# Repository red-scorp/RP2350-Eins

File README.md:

```
  _____  _____ ___  ____  _____  ___         ______ _____ _   _  _____ 
 |  __ \|  __ \__ \|___ \| ____|/ _ \       |  ____|_   _| \ | |/ ____|
 | |__) | |__) | ) | __) | |__ | | | |______| |__    | | |  \| | (___  
 |  _  /|  ___/ / / |__ <|___ \| | | |______|  __|   | | | . ` |\___ \ 
 | | \ \| |    / /_ ___) |___) | |_| |      | |____ _| |_| |\  |____) |
 |_|  \_\_|   |____|____/|____/ \___/       |______|_____|_| \_|_____/ 
```

# RP2350-Eins Project

The **RP2350-Eins** project aims to create a replacement for the Arduino UNO R3 or Arduino M0 using the RP2350 MCU.
This project was born as a continuation my previous project, [RP2040-Eins](https://github.com/red-scorp/RP2040-Eins), which was based on the Raspberry Pi RP2040 MCU.

## RP2350-Eins Board

The **RP2350-Eins** board is a 4-layer design intended to accommodate the popular Raspberry Pi RP2350 MCU within the standard Arduino UNO R3 footprint.

This board is crafted in Germany, and its name, "RP2350-Eins", incorporates the German word "Eins" (pronounced as "eye-ns"), which translates to "one". This name choice reflects the use of the same form-factor as the Arduino "Uno", which means "one" in Italian.

Preview:

You can view the [Schematics in PDF format](doc/RP2350-Eins.pdf) for detailed information.

STEP 3D file is available [with pins](doc/RP2350-Eins.step).

Features:

- Arduino UNO compatible pinout
- Partially compatible with Arduino Nano RP2350 Connect pinout
- Dual-core Cortex-M0+ Raspberry Pi RP2350
- 21 GPIO pins, including 4 analog inputs
- USB Type-C connector
- JTAG and DBG debugging connectors
- LDO-based 5V and 3.3V power supply with a maximum 12V input
- Supports both SOIC and WSON 16MB flash packages
- Includes power, user and RGB LEDs

CAM files, as well as the BOM and CPL files for JLCPCB, are available.

### Board Pinout

Following pinout is used for the board:

| Board Pin | RP2350 Pin | Function | Notes |
| --------- | ---------- | -------- | ----- |
| D0        | GPIO1      | UART0 TX |       |
| D1        | GPIO0      | UART0 RX |       |
| D2        | GPIO25     |          |       |
| D3        | GPIO15     |          |       |
| D4        | GPIO16     |          |       |
| D5        | GPIO17     |          |       |
| D6        | GPIO18     |          |       |
| D7        | GPIO19     |          |       |
| D8        | GPIO20     |          |       |
| D9        | GPIO21     |          |       |
| D10       | GPIO5      | SS       |       |
| D11       | GPIO7      | MOSI     |       |
| D12       | GPIO4      | MISO     |       |
| D13       | GPIO6      | SCK      | LED   |
| D14 A0    | GPIO26     |          |       |
| D15 A1    | GPIO27     |          |       |
| D16 A2    | GPIO28     |          |       |
| D17 A3    | GPIO29     |          |       |
| D18       | GPIO12     | SDA      |       |
| D19       | GPIO13     | SCL      |       |
| D20       | GPIO22     |          |       |
| D21       | GPIO23     |          |       |
| LED_R     | GPIO9      |          |       |
| LED_G     | GPIO10     |          |       |
| LED_B     | GPIO11     |          |       |

## Version History

This board exists in a single LDO-based flavor. If you want to use a Buck-based version of this board, please contact me directly.

Each version of the board listed below is tagged in the repository. You can use the tag to checkout the repository to the specific version.

### v1.0b1 - xx.xx.2024

Initial release for testing purposes.

## Links

- [Raspberry Pi RP2350 information page](https://www.raspberrypi.com/documentation/microcontrollers/silicon.html#rp2350).
- [Arduino UNO R3 information page](https://docs.arduino.cc/retired/boards/arduino-uno-rev3-with-long-pins).
- [Arduino SDK for RP2040/RP2350 board](https://github.com/earlephilhower/arduino-pico).

## How to Help

Your contributions as code, resources, or finances are welcome! Please contact me directly via email at andriy.golovnya@gmail.com or through my [GitHub profile](https://github.com/red-scorp).

If you'd like to make a financial contribution, you can donate via [PayPal](http://paypal.me/redscorp) or [Ko-Fi](http://ko-fi.com/redscorp). Your support is greatly appreciated.

Thanks in advance!

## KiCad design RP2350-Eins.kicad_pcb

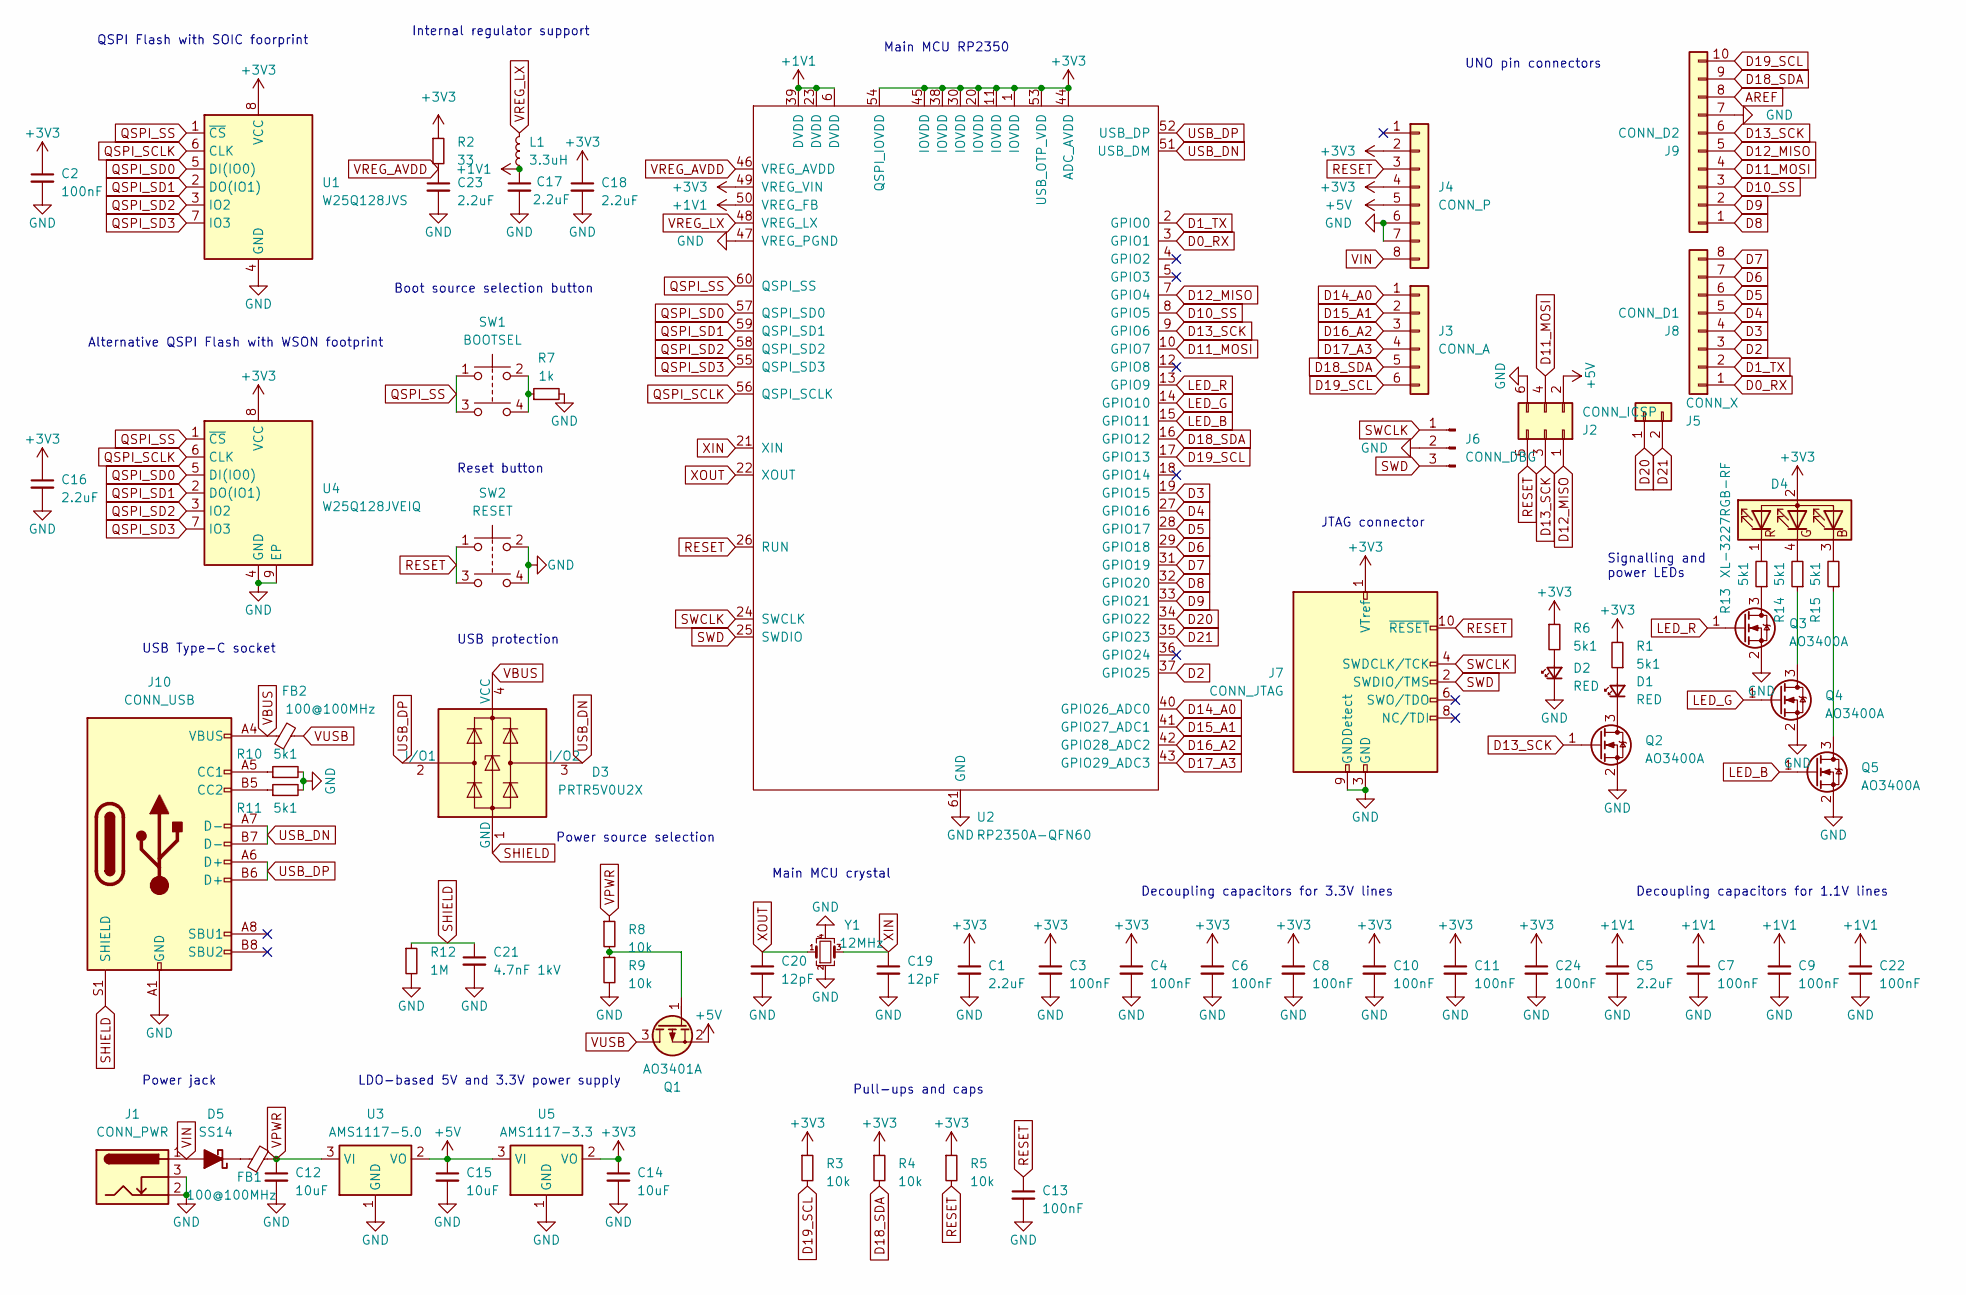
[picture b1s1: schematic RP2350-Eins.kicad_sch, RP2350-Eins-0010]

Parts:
C1, C5, C16, C17, C18, C23: 2.2uF; C_0603_1608Metric
C2, C3, C4, C6, C7, C8, C9, C10, C11, C13, C22, C24: 100nF; C_0402_1005Metric
C12, C14, C15: 10uF; C_0805_2012Metric
C19, C20: 12pF; C_0402_1005Metric
C21: 4.7nF 1kV; C_1206_3216Metric
D1, D2: RED; LED_0603_1608Metric
D3: PRTR5V0U2X; SOT-143
D4: XL-3227RGB-RF; LED_RGB_1210
D5: SS14; D_DO-214AC_SMA
FB1, FB2: 100@100MHz; L_0805_2012Metric
J1: CONN_PWR; BarrelJack_Horizontal
J2: CONN_ICSP; PinHeader_2x03_P2.54mm_Vertical
J3: CONN_A; PinSocket_1x06_P2.54mm_Vertical
J4: CONN_P; PinSocket_1x08_P2.54mm_Vertical
J5: CONN_X; PinHeader_1x02_P2.54mm_Vertical
J6: CONN_DBG; PinHeader_1x03_P2.54mm_Vertical
J7: CONN_JTAG; PinHeader_2x05_P1.27mm_Vertical
J8: CONN_D1; PinSocket_1x08_P2.54mm_Vertical
J9: CONN_D2; PinSocket_1x10_P2.54mm_Vertical
J10: CONN_USB; USB_C_Receptacle_HRO_TYPE-C-31-M-12
L1: 3.3uH; L_0805_2012Metric
Q1: AO3401A; SOT-23
Q2, Q3, Q4, Q5: AO3400A; SOT-23
R1, R6, R10, R11, R13, R14, R15: 5k1; R_0402_1005Metric
R2: 33; R_0402_1005Metric
R3, R4, R5, R8, R9: 10k; R_0402_1005Metric
R7: 1k; R_0402_1005Metric
R12: 1M; R_0603_1608Metric
SW1: BOOTSEL; Button_Tact_Sqkg
SW2: RESET; Button_Tact_Sqkg
U1: W25Q128JVS; SOIC-8_5.23x5.23mm_P1.27mm
U2: RP2350A-QFN60; RP2350A_QFN-60_EP_7.75x7.75_Pitch0.4mm
U3: AMS1117-5.0; SOT-223-3_TabPin2
U4: W25Q128JVEIQ; WSON-8-1EP_6x5mm_P1.27mm_EP3.4x4.3mm
U5: AMS1117-3.3; SOT-223-3_TabPin2
Y1: 12MHz; Crystal_SMD_3225-4Pin_3.2x2.5mm

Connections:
+1V1: C5.1, C7.1, C9.1, C17.1, C22.1, L1.1, U2.6 (DVDD), U2.23 (DVDD), U2.39 (DVDD), U2.50 (VREG_FB)
+3V3: C1.1, C2.1, C3.1, C4.1, C6.1, C8.1, C10.1, C11.1, C14.1, C16.1, C18.1, C24.1, D4.2 (A), J4.2, J4.4, J7.1 (VTref), R1.2, R2.1, R3.1, R4.1, R5.1, R6.1, U1.8 (VCC), U2.1 (IOVDD), U2.11 (IOVDD), U2.20 (IOVDD), U2.30 (IOVDD), U2.38 (IOVDD), U2.44 (ADC_AVDD), U2.45 (IOVDD), U2.49 (VREG_VIN), U2.53 (USB_OTP_VDD), U2.54 (QSPI_IOVDD), U4.8 (VCC), U5.2 (VO)
+5V: C15.1, J2.2, J4.5, Q1.2 (S), U3.2 (VO), U5.3 (VI)
AREF: J9.8
D0_RX: J8.1, U2.3 (GPIO1)
D1_TX: J8.2, U2.2 (GPIO0)
D2: J8.3, U2.37 (GPIO25)
D3: J8.4, U2.19 (GPIO15)
D4: J8.5, U2.27 (GPIO16)
D5: J8.6, U2.28 (GPIO17)
D6: J8.7, U2.29 (GPIO18)
D7: J8.8, U2.31 (GPIO19)
D8: J9.1, U2.32 (GPIO20)
D9: J9.2, U2.33 (GPIO21)
D10_SS: J9.3, U2.8 (GPIO5)
D11_MOSI: J2.4, J9.4, U2.10 (GPIO7)
D12_MISO: J2.1, J9.5, U2.7 (GPIO4)
D13_SCK: J2.3, J9.6, Q2.1 (G), U2.9 (GPIO6)
D14_A0: J3.1, U2.40 (GPIO26_ADC0)
D15_A1: J3.2, U2.41 (GPIO27_ADC1)
D16_A2: J3.3, U2.42 (GPIO28_ADC2)
D17_A3: J3.4, U2.43 (GPIO29_ADC3)
D18_SDA: J3.5, J9.9, R4.2, U2.16 (GPIO12)
D19_SCL: J3.6, J9.10, R3.2, U2.17 (GPIO13)
D20: J5.1, U2.34 (GPIO22)
D21: J5.2, U2.35 (GPIO23)
GND: C1.2, C2.2, C3.2, C4.2, C5.2, C6.2, C7.2, C8.2, C9.2, C10.2, C11.2, C12.2, C13.2, C14.2, C15.2, C16.2, C17.2, C18.2, C19.2, C20.2, C21.2, C22.2, C23.2, C24.2, D2.1 (K), J1.2, J1.3, J2.6, J4.6, J4.7, J6.2, J7.3 (GND), J7.5 (GND), J7.9 (GNDDetect), J9.7, J10.A1 (GND), J10.A12 (GND), J10.B1 (GND), J10.B12 (GND), Q2.2 (S), Q3.2 (S), Q4.2 (S), Q5.2 (S), R7.2, R9.2, R10.2, R11.2, R12.2, SW2.2, SW2.4, U1.4 (GND), U2.47 (VREG_PGND), U2.61 (GND), U3.1 (GND), U4.4 (GND), U4.9 (EP), U5.1 (GND), Y1.2, Y1.4
LED_B: Q5.1 (G), U2.15 (GPIO11)
LED_G: Q4.1 (G), U2.14 (GPIO10)
LED_R: Q3.1 (G), U2.13 (GPIO9)
unnamed: D1.2 (A), R1.1
unnamed: D1.1 (K), Q2.3 (D)
unnamed: D2.2 (A), R6.2
unnamed: D4.3 (BK), R15.2
unnamed: D4.4 (GK), R14.2
unnamed: D4.1 (RK), R13.2
unnamed: D5.1 (K), FB1.1
unnamed: J10.A5 (CC1), R10.1
unnamed: J10.B5 (CC2), R11.1
unnamed: Q1.1 (G), R8.2, R9.1
unnamed: Q3.3 (D), R13.1
unnamed: Q4.3 (D), R14.1
unnamed: Q5.3 (D), R15.1
unnamed: R7.1, SW1.2, SW1.4
QSPI_SCLK: U1.6 (CLK), U2.56 (QSPI_SCLK), U4.6 (CLK)
QSPI_SD0: U1.5 (DI(IO0)), U2.57 (QSPI_SD0), U4.5 (DI(IO0))
QSPI_SD1: U1.2 (DO(IO1)), U2.59 (QSPI_SD1), U4.2 (DO(IO1))
QSPI_SD2: U1.3 (IO2), U2.58 (QSPI_SD2), U4.3 (IO2)
QSPI_SD3: U1.7 (IO3), U2.55 (QSPI_SD3), U4.7 (IO3)
QSPI_SS: SW1.1, SW1.3, U1.1 (~CS), U2.60 (QSPI_SS), U4.1 (~CS)
RESET: C13.1, J2.5, J4.3, J7.10 (~RESET), R5.2, SW2.1, SW2.3, U2.26 (RUN)
SHIELD: C21.1, D3.1 (GND), J10.S1 (SHIELD), R12.1
SWCLK: J6.1, J7.4 (SWDCLK/TCK), U2.24 (SWCLK)
SWD: J6.3, J7.2 (SWDIO/TMS), U2.25 (SWDIO)
USB_DN: D3.3 (I/O2), J10.A7 (D-), J10.B7 (D-), U2.51 (USB_DM)
USB_DP: D3.2 (I/O1), J10.A6 (D+), J10.B6 (D+), U2.52 (USB_DP)
VBUS: D3.4 (VCC), FB2.1, J10.A4 (VBUS), J10.A9 (VBUS), J10.B4 (VBUS), J10.B9 (VBUS)
VIN: D5.2 (A), J1.1, J4.8
VPWR: C12.1, FB1.2, R8.1, U3.3 (VI)
VREG_AVDD: C23.1, R2.2, U2.46 (VREG_AVDD)
VREG_LX: L1.2, U2.48 (VREG_LX)
VUSB: FB2.2, Q1.3 (D)
XIN: C19.1, U2.21 (XIN), Y1.3
XOUT: C20.1, U2.22 (XOUT), Y1.1

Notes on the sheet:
USB protection
Alternative QSPI Flash with WSON footprint
UNO pin connectors
Main MCU RP2350
Power source selection
Power jack
Decoupling capacitors for 3.3V lines
Main MCU crystal
Internal regulator support
Decoupling capacitors for 1.1V lines
Pull-ups and caps
Signalling and power LEDs
JTAG connector
Reset button
USB Type-C socket
Boot source selection button
LDO-based 5V and 3.3V power supply
QSPI Flash with SOIC foorprint

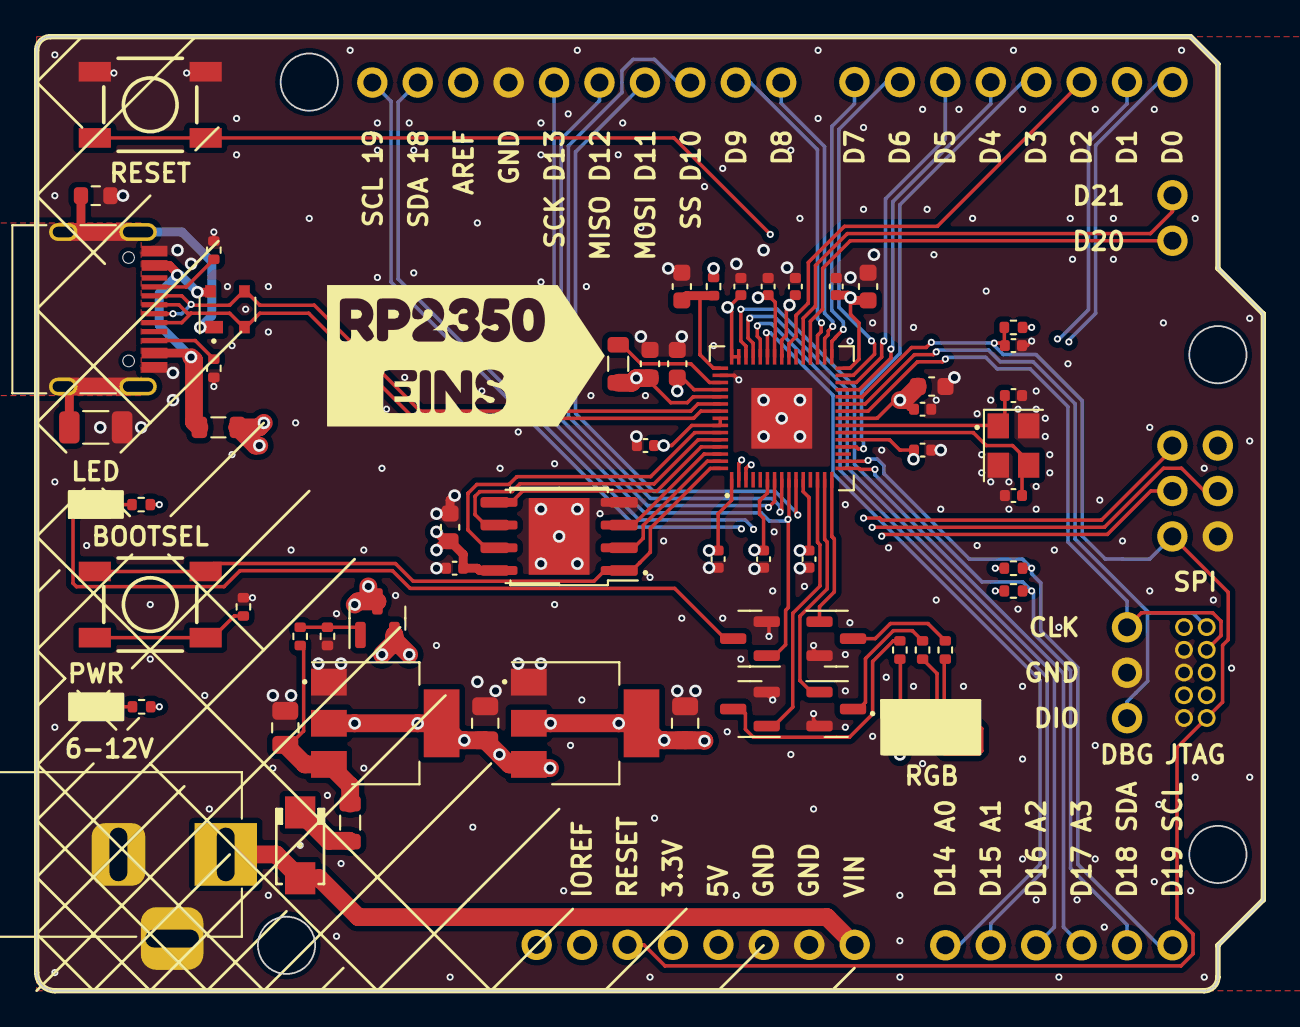
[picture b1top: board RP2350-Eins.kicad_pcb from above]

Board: 4 copper layers, 68.6 x 53.3 mm, 72 parts (1 on the bottom side), 63 nets.

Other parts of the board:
G1: QR-CODE; LOGO
G2: G***; kibuzzard-66CA2205

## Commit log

2024-08-24 Added base for the board, based on previous design
2024-08-24 Added missing components. Routed the board.
2024-08-25 Added few vias. Moved staff around.
2024-08-25 Added README and FUNDING files.
2024-08-25 Moved staff around.
2024-08-31 Use manual vias under RP2350 instead of from footprint
2024-09-22 Generated PNG preview
2024-09-22 Generated PDF schematics
2024-09-22 Generated CAM file
2024-09-22 Generated STEP 3D model
2024-09-22 Added generic JLCPCB BOM
2024-09-22 Added generic JLCPCB CPL
2024-09-22 Some parameter changes

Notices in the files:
RP2350-Eins.kicad_pcb:
(c) 2024 Andriy Golovnya
